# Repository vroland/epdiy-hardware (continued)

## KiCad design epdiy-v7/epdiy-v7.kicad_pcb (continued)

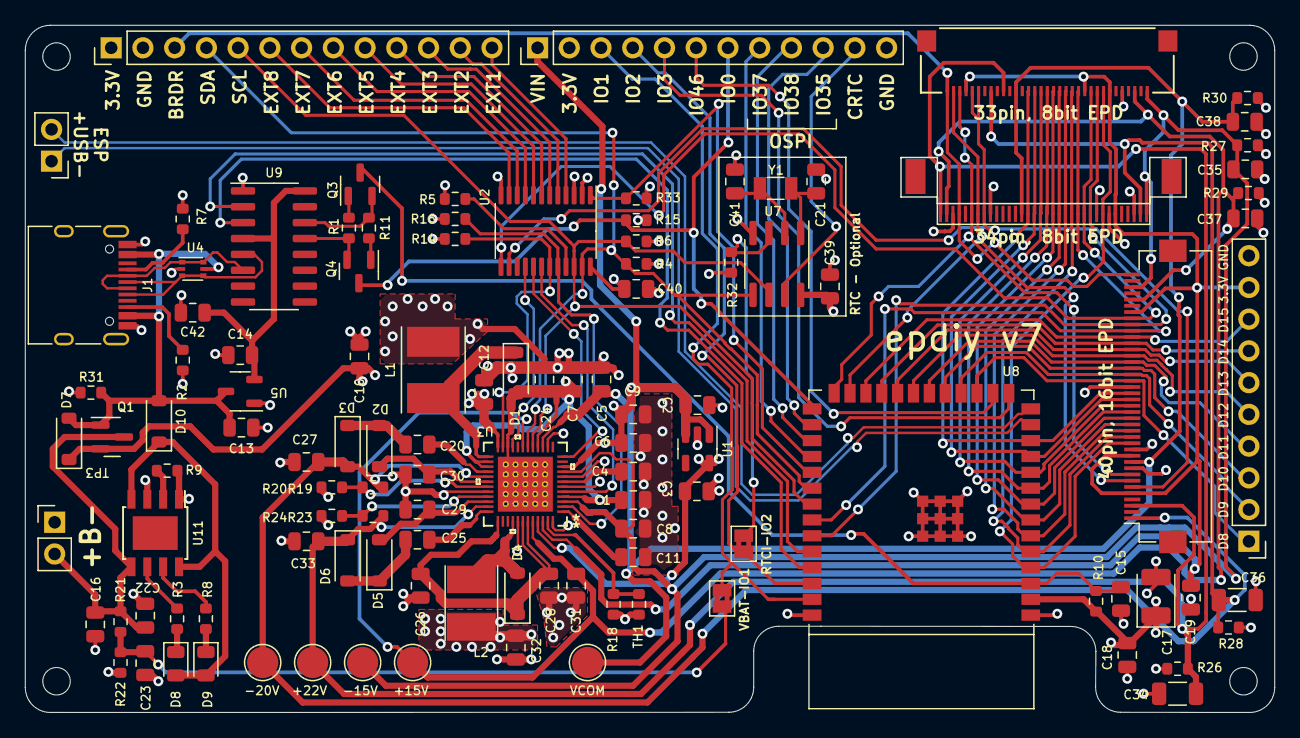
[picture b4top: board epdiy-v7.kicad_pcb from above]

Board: 4 copper layers, 100.0 x 55.0 mm, 117 parts (0 on the bottom side), 100 nets.

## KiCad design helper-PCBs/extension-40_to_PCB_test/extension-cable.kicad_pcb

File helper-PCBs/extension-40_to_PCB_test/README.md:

## What it is

This PCB is just a tester that comes handy if you want to check that all GPIOs, the 16 data lines plus other 7 signals, are correctly soldered in your PCB.
After this comes just need to make a easy program, put all GPIOs in an array, and sequence them HIGH/ LOW.

NOTE: This needs a 40 pin Reversed cable in order to be connected to epdiy v7

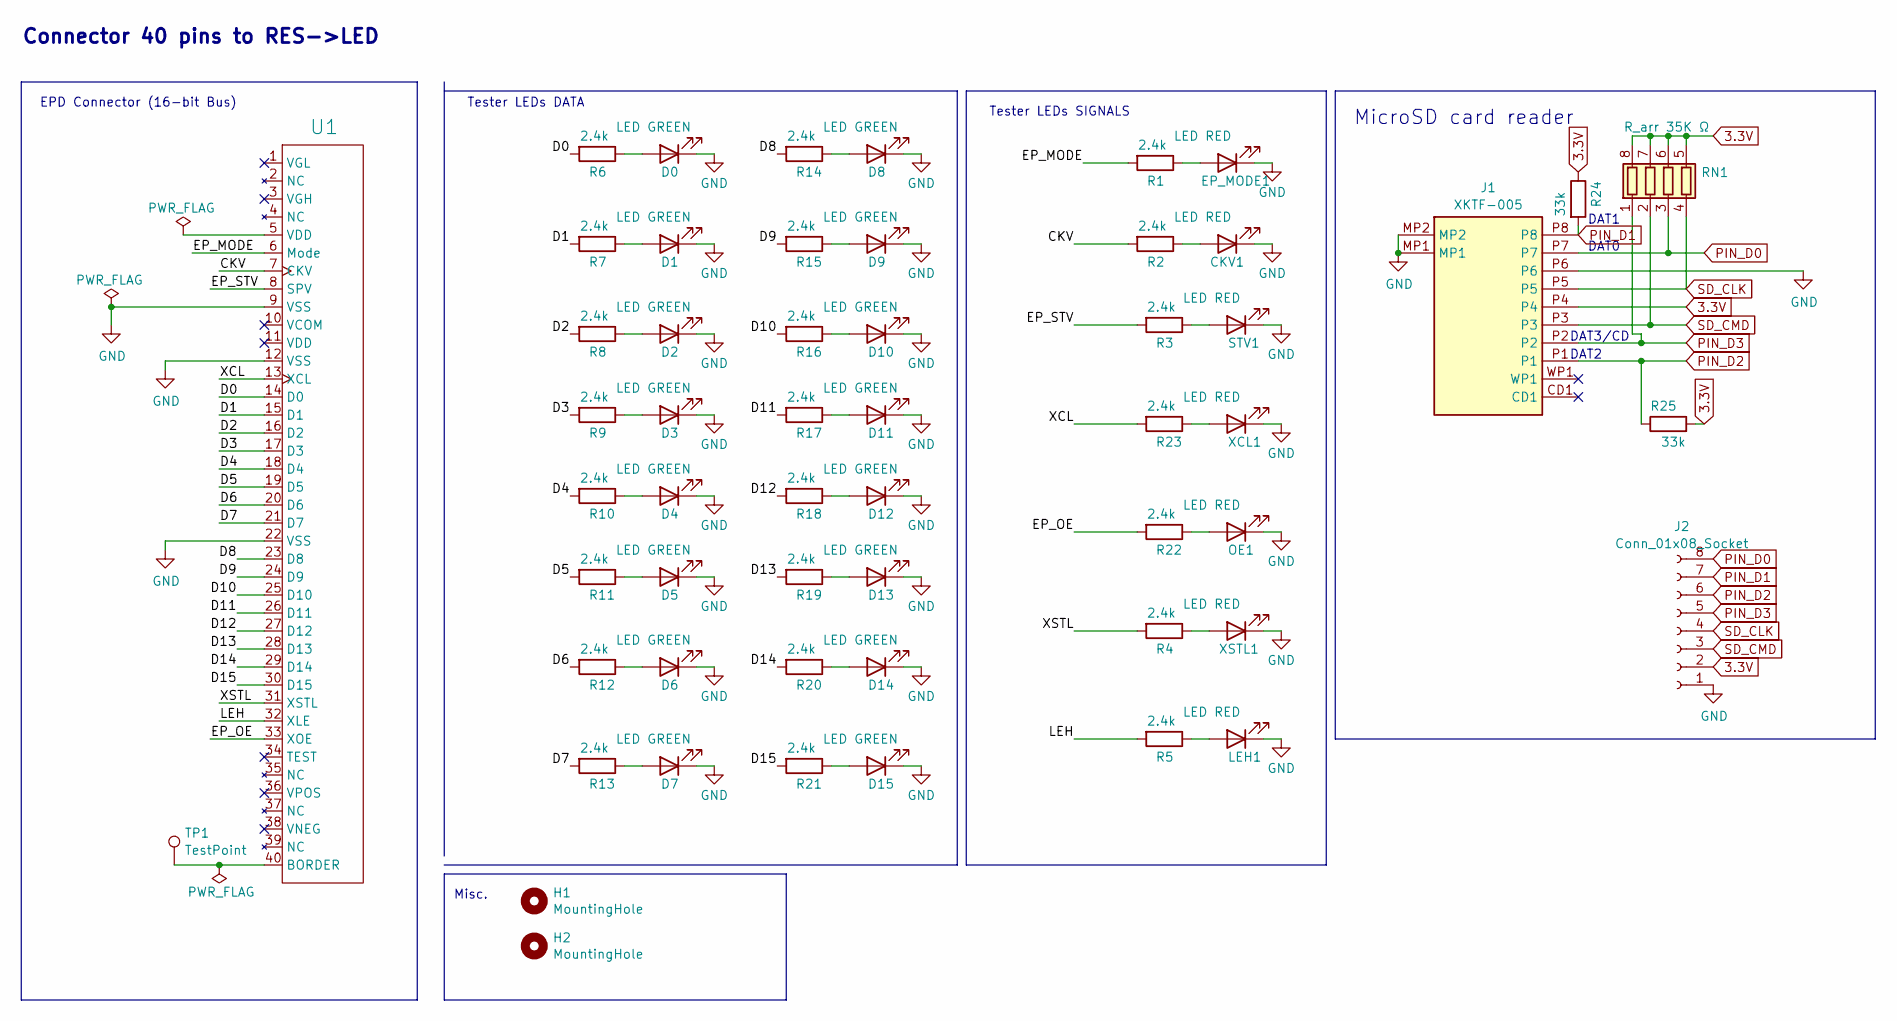
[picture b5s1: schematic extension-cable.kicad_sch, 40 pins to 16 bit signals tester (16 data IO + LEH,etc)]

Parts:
CKV1: LED RED; LED_0805_2012Metric; LCSC C84256
D0, D1, D2, D3, D4, D5, D6, D7, D8, D9, D10, D11, D12, D13, D14, D15: LED GREEN; LED_0805_2012Metric; LCSC C2297
EP_MODE1: LED RED; LED_0805_2012Metric; LCSC C84256
H1, H2: MountingHole; MountingHole_2.2mm_M2
J1: XKTF-005; XKTF005-SD; Manufacturer_Part_Number XKTF-005; LCSC C2689687
J2: Conn_01x08_Socket; PinSocket_1x08_P2.54mm_Vertical
LEH1: LED RED; LED_0805_2012Metric; LCSC C84256
OE1: LED RED; LED_0805_2012Metric; LCSC C84256
R1, R2, R3, R4, R5, R6, R7, R8, R9, R10, R11, R12, R13, R14, R15, R16, R17, R18, R19, R20, R21, R22, R23: 2.4k; R_0603_1608Metric; LCSC C22940
R24, R25: 33k; R_0603_1608Metric; LCSC C4216
RN1: R_arr 35K Ω; SMT_F392JTCE_UNR_SD-pullup; LCSC C425297
STV1: LED RED; LED_0805_2012Metric; LCSC C84256
TP1: TestPoint; TestPoint_Pad_2.0x2.0mm
U1: ED078KH6; FH1240S05SH55; LCSC C202114
XCL1: LED RED; LED_0805_2012Metric; LCSC C84256
XSTL1: LED RED; LED_0805_2012Metric; LCSC C84256

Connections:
3.3V: J1.P4, J2.2, R24.1, R25.2, RN1.5 (R4.2), RN1.6 (R3.2), RN1.7 (R2.2), RN1.8 (R1.2)
/CKV: R2.2, U1.7 (CKV)
/D0: R6.2, U1.14 (D0)
/D1: R7.2, U1.15 (D1)
/D2: R8.2, U1.16 (D2)
/D3: R9.2, U1.17 (D3)
/D4: R10.2, U1.18 (D4)
/D5: R11.2, U1.19 (D5)
/D6: R12.2, U1.20 (D6)
/D7: R13.2, U1.21 (D7)
/D8: R14.2, U1.23 (D8)
/D9: R15.2, U1.24 (D9)
/D10: R16.2, U1.25 (D10)
/D11: R17.2, U1.26 (D11)
/D12: R18.2, U1.27 (D12)
/D13: R19.2, U1.28 (D13)
/D14: R20.2, U1.29 (D14)
/D15: R21.2, U1.30 (D15)
/EP_MODE: R1.2, U1.6 (Mode)
/EP_OE: R22.2, U1.33 (XOE)
/EP_STV: R3.2, U1.8 (SPV)
/LEH: R5.2, U1.32 (XLE)
/XCL: R23.2, U1.13 (XCL)
/XSTL: R4.2, U1.31 (XSTL)
unnamed: CKV1.2 (A), R2.1
unnamed: D0.2 (A), R6.1
unnamed: D1.2 (A), R7.1
unnamed: D2.2 (A), R8.1
unnamed: D3.2 (A), R9.1
unnamed: D4.2 (A), R10.1
unnamed: D5.2 (A), R11.1
unnamed: D6.2 (A), R12.1
unnamed: D7.2 (A), R13.1
unnamed: D8.2 (A), R14.1
unnamed: D9.2 (A), R15.1
unnamed: D10.2 (A), R16.1
unnamed: D11.2 (A), R17.1
unnamed: D12.2 (A), R18.1
unnamed: D13.2 (A), R19.1
unnamed: D14.2 (A), R20.1
unnamed: D15.2 (A), R21.1
unnamed: EP_MODE1.2 (A), R1.1
unnamed: LEH1.2 (A), R5.1
unnamed: OE1.2 (A), R22.1
unnamed: R3.1, STV1.2 (A)
unnamed: R23.1, XCL1.2 (A)
unnamed: R4.1, XSTL1.2 (A)
PIN_D0: J1.P7, J2.8, RN1.3 (R3.1)
PIN_D1: J1.P8, J2.7, R24.2
PIN_D2: J1.P1, J2.6, R25.1
PIN_D3: J1.P2, J2.5, RN1.1 (R1.1)
SD_CLK: J1.P5, J2.4, RN1.4 (R4.1)
SD_CMD: J1.P3, J2.3, RN1.2 (R2.1)

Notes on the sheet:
DAT0
Tester LEDs SIGNALS
MicroSD card reader
Misc.
Tester LEDs DATA
Connector 40 pins to RES->LED
EPD Connector (16-bit Bus)
DAT1
DAT3/CD
DAT2

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
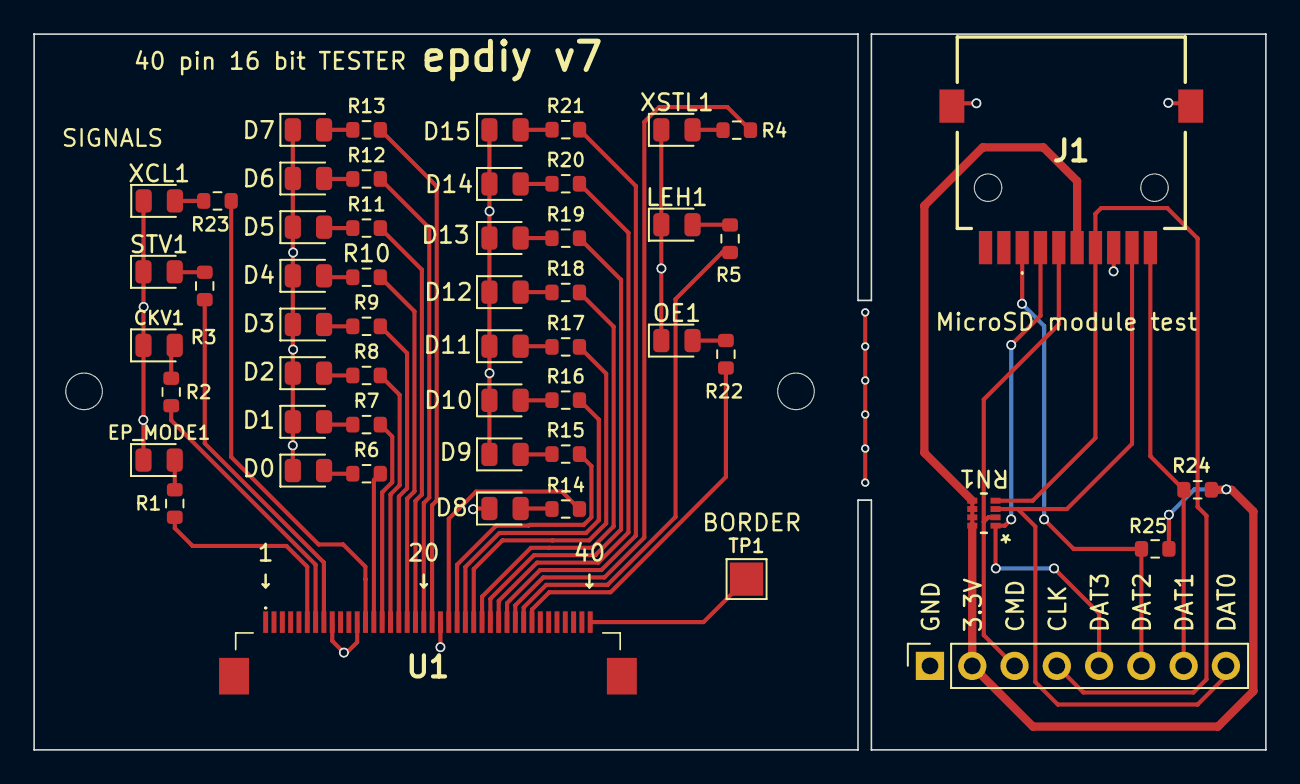
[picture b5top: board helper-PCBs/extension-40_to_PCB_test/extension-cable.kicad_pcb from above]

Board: 2 copper layers, 74.0 x 43.0 mm, 55 parts (0 on the bottom side), 55 nets.

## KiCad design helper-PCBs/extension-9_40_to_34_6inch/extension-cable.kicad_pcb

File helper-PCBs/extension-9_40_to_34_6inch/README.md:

## What it is

This PCB is an adapter from 9.7" (33 pins) and 40 pins (16 bit output) to 33 pins (6" output)

It can come handy if you design a PCB that has no 33 pin connector. Or also to connect two 6" epaper, that will work showing exactly the same content, to any of the controlling boards.

Design: Martin Fasani  based on @vroland work.

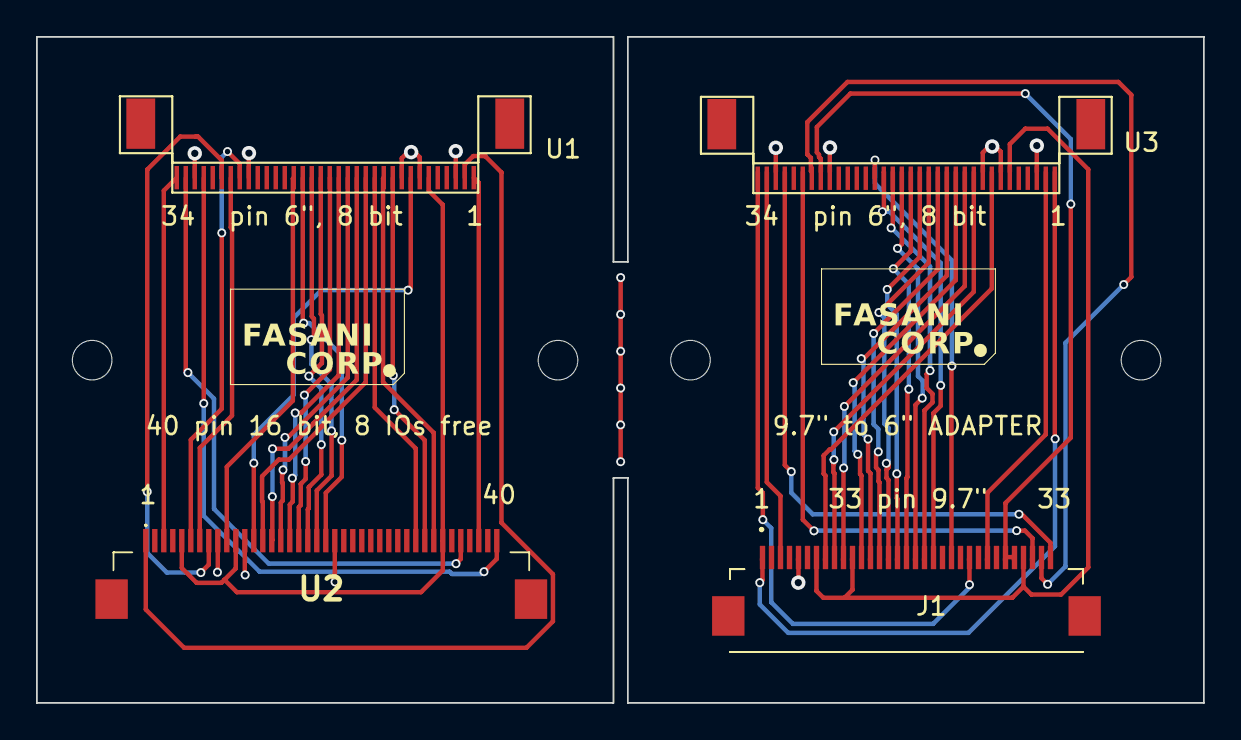
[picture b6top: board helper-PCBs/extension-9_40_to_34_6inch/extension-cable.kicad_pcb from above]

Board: 2 copper layers, 64.8 x 37.0 mm, 8 parts (0 on the bottom side), 45 nets.

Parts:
H1, H2, H3, H4: MountingHole; MountingHole_2.2mm_M2
J1: XF2M-3315-1A; FH1233S05SH55
U1, U3: ED060XC5; X05A20H34G
U2: ED078KH6; FH1240S05SH55

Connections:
/15V: U1.33 (VPOS), U2.36 (VPOS)
/15V_A: J1.3 (VPOS), U3.33 (VPOS)
/+22V: U1.34 (VGG), U2.3 (VGH)
/+22V_A: J1.24 (VGG), U3.34 (VGG)
/-15V: U1.1 (VNEG), U2.38 (VNEG)
/-15V_A: J1.1 (VNEG), U3.1 (VNEG)
/-20V: U1.2 (VEE), U2.1 (VGL)
/-20V_A: J1.26 (VEE), U3.2 (VEE)
/BORDER: U1.31 (BORDER), U2.40 (BORDER)
/BORDER_A: J1.33 (BORDER), U3.31 (BORDER)
/CKV: U1.28 (CKV), U2.7 (CKV)
/CKV_A: J1.32 (CKV), U3.28 (CKV)
/D0: U1.13 (D0), U2.14 (D0)
/D0_A: J1.13 (D0), U3.13 (D0)
/D1: U1.14 (D1), U2.15 (D1)
/D1_A: J1.14 (D1), U3.14 (D1)
/D2: U1.15 (D2), U2.16 (D2)
/D2_A: J1.15 (D2), U3.15 (D2)
/D3: U1.16 (D3), U2.17 (D3)
/D3_A: J1.16 (D3), U3.16 (D3)
/D4: U1.17 (D4), U2.18 (D4)
/D4_A: J1.17 (D4), U3.17 (D4)
/D5: U1.18 (D5), U2.19 (D5)
/D5_A: J1.18 (D5), U3.18 (D5)
/D6: U1.19 (D6), U2.20 (D6)
/D6_A: J1.19 (D6), U3.19 (D6)
/D7: U1.20 (D7), U2.21 (D7)
/D7_A: J1.20 (D7), U3.20 (D7)
/EP_MODE: U1.27 (MODE1), U2.6 (Mode)
/EP_MODE_A: J1.28 (MODE2), J1.29 (MODE1), U3.27 (MODE1)
/EP_OE: U1.11 (XOE), U2.33 (XOE)
/EP_OE_A: J1.10 (OEH), U3.11 (XOE)
/EP_STV: U1.29 (SPV), U2.8 (SPV)
/EP_STV_A: J1.31 (STV), U3.29 (SPV)
/EP_VCOM: U1.21 (VCOM), U2.10 (VCOM)
/EP_VCOM_A: J1.22 (VCOM), U3.21 (VCOM)
/LEH: U1.10 (XLE), U2.32 (XLE)
/LEH_A: J1.9 (LEH), U3.10 (XLE)
/XCL: U1.8 (XCL), U2.13 (XCL)
/XCL_A: J1.8 (CKH), U3.8 (XCL)
/XSTL: U1.12 (XSTL), U2.31 (XSTL)
/XSTL_A: J1.12 (STH), U3.12 (XSTL)
EPD_VDD: U1.6 (VDD), U2.5 (VDD), U2.11 (VDD), U2.34 (TEST)
EPD_VDD_A: J1.7 (VDD), J1.11 (RL), J1.30 (UD), U3.6 (VDD)
GND: J1.5 (VSS), U1.3 (VSS), U1.7 (VSS), U1.9 (VSS), U1.26 (VSS), U1.32 (VSS), U2.9 (VSS), U2.12 (VSS), U2.22 (VSS), U3.3 (VSS), U3.7 (VSS), U3.9 (VSS), U3.26 (VSS), U3.32 (VSS)

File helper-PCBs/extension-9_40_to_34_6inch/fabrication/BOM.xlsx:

Designator | Footprint | Comments | JLCPCB Part #
J1 | FH1233S05SH55 | XF2M-3315-1A | C597986
U1,U3 | X05A20H34G | ED060XC5 | C528053
U2 | FH1240S05SH55 | ED078KH6 | C202114
